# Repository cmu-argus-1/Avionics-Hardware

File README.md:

# AVIONICS_HARDWARE_DEV

Hardware boards devolepment repository.
1. Magnetic torque coil board
2. Power board
3. ML board
4. Camera board

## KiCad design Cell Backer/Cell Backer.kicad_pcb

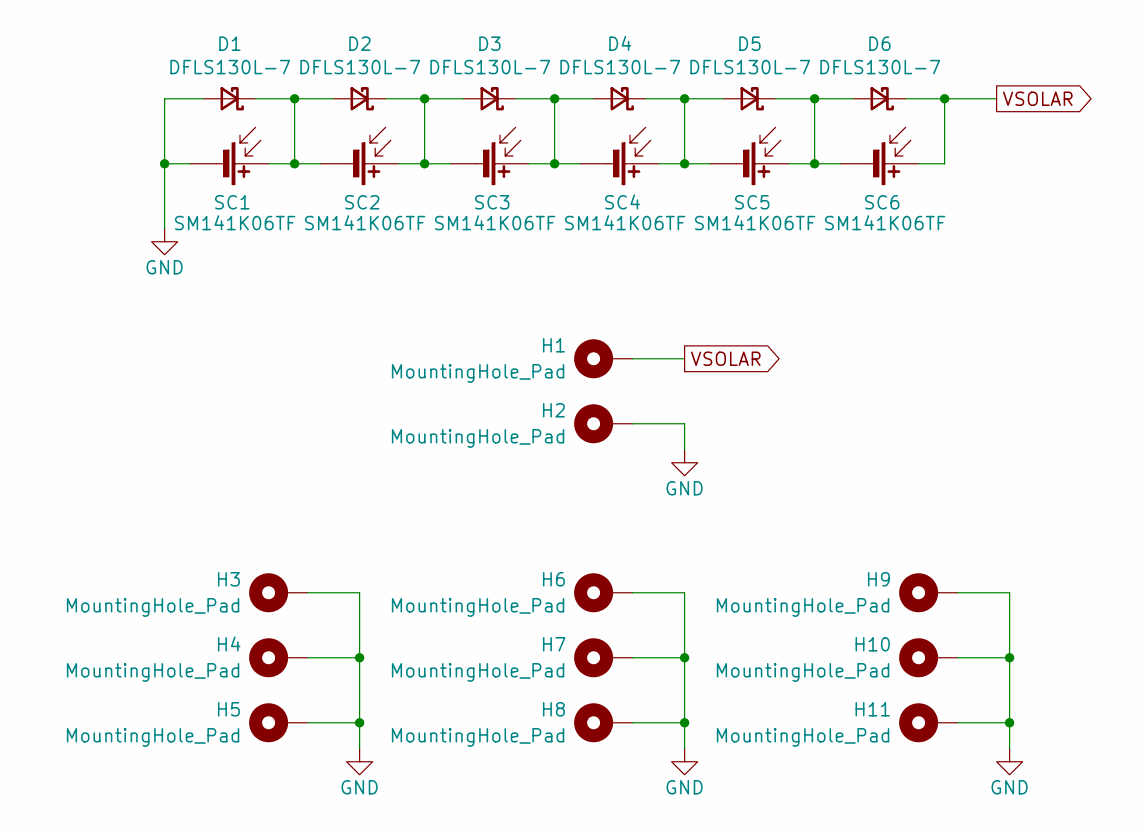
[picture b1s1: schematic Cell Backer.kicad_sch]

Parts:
D1, D2, D3, D4, D5, D6: DFLS130L-7; D_PowerDI-123
H1, H2: MountingHole_Pad; MountingHole_1.5mm
H3, H4, H5, H6, H7, H8, H9, H10, H11: MountingHole_Pad; MountingHole_1mm
SC1, SC2, SC3, SC4, SC5, SC6: SM141K06TF

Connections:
GND: D1.2 (A), H2.1, H3.1, H4.1, H5.1, H6.1, H7.1, H8.1, H9.1, H10.1, H11.1, SC1.2 (-)
unnamed: D1.1 (K), D2.2 (A), SC1.1 (+), SC2.2 (-)
unnamed: D2.1 (K), D3.2 (A), SC2.1 (+), SC3.2 (-)
unnamed: D3.1 (K), D4.2 (A), SC3.1 (+), SC4.2 (-)
unnamed: D4.1 (K), D5.2 (A), SC4.1 (+), SC5.2 (-)
unnamed: D5.1 (K), D6.2 (A), SC5.1 (+), SC6.2 (-)
VSOLAR: D6.1 (K), H1.1, SC6.1 (+)

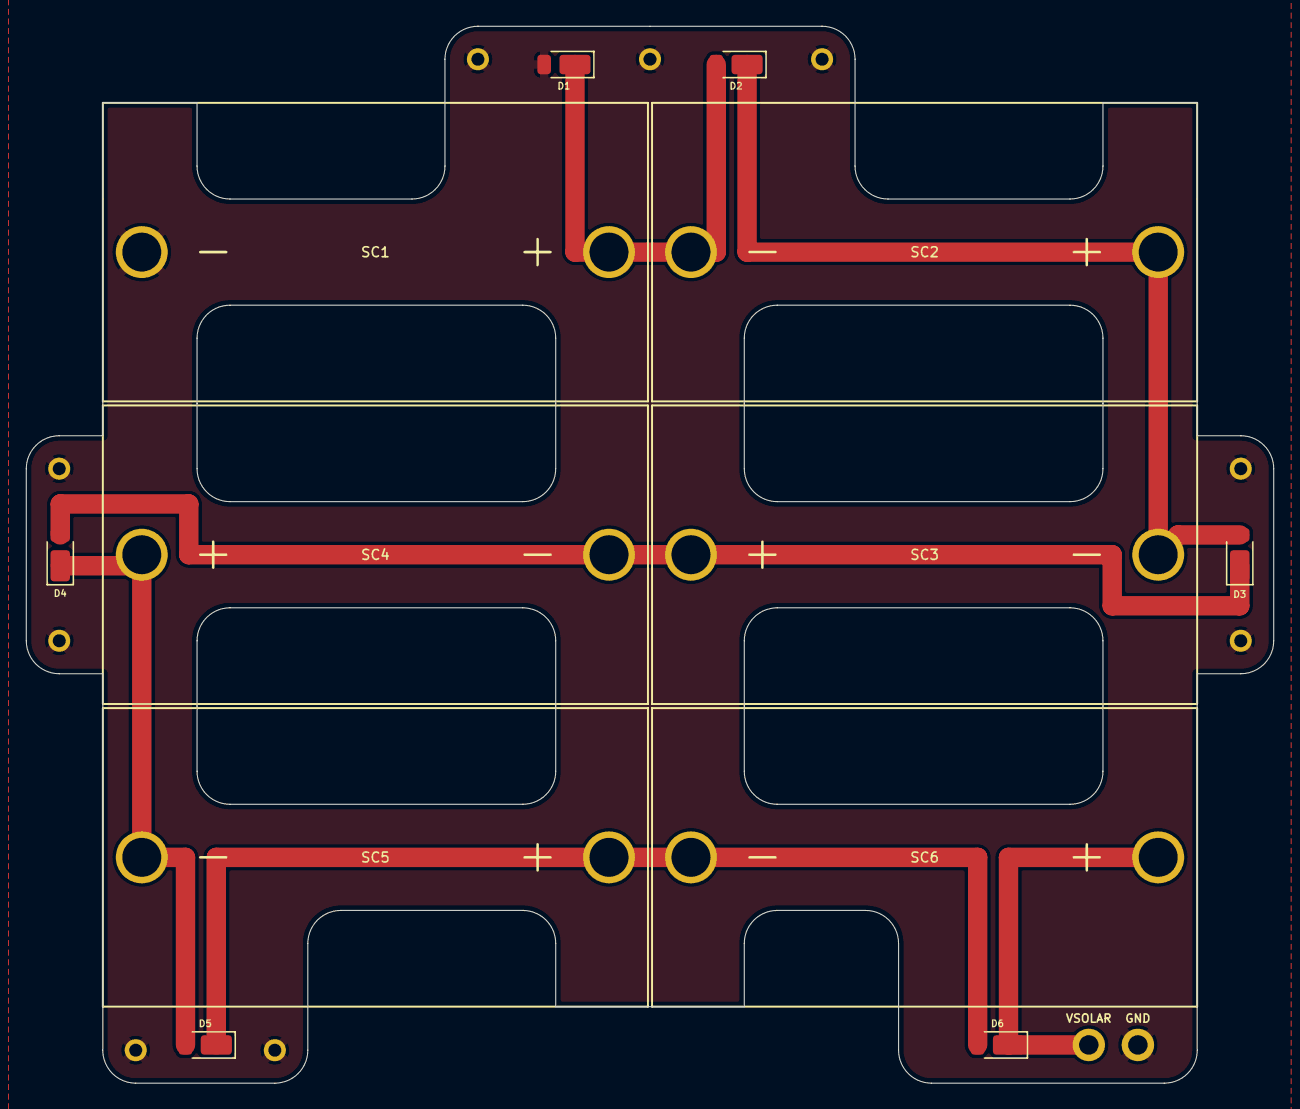
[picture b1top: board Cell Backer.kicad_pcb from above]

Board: 2 copper layers, 96.1 x 81.4 mm, 23 parts (0 on the bottom side), 7 nets.

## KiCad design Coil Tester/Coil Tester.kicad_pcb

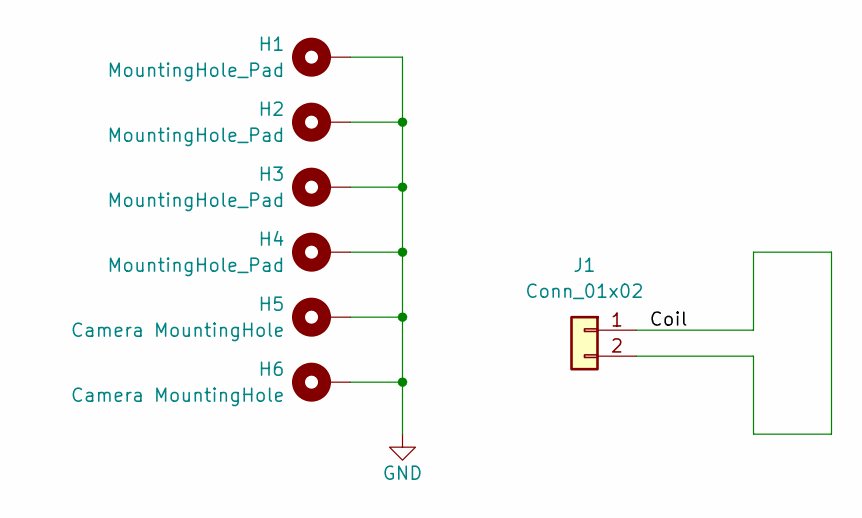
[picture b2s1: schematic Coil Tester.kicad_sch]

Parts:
H1, H2, H3, H4: MountingHole_Pad; MountingHole_3.2mm_M3_DIN965_Pad_TopBottom
H5, H6: Camera MountingHole; MountingHole_3mm
J1: Conn_01x02; PinHeader_1x02_P2.54mm_Vertical

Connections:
/Coil: J1.1, J1.2
GND: H1.1, H2.1, H3.1, H4.1, H5.1, H6.1

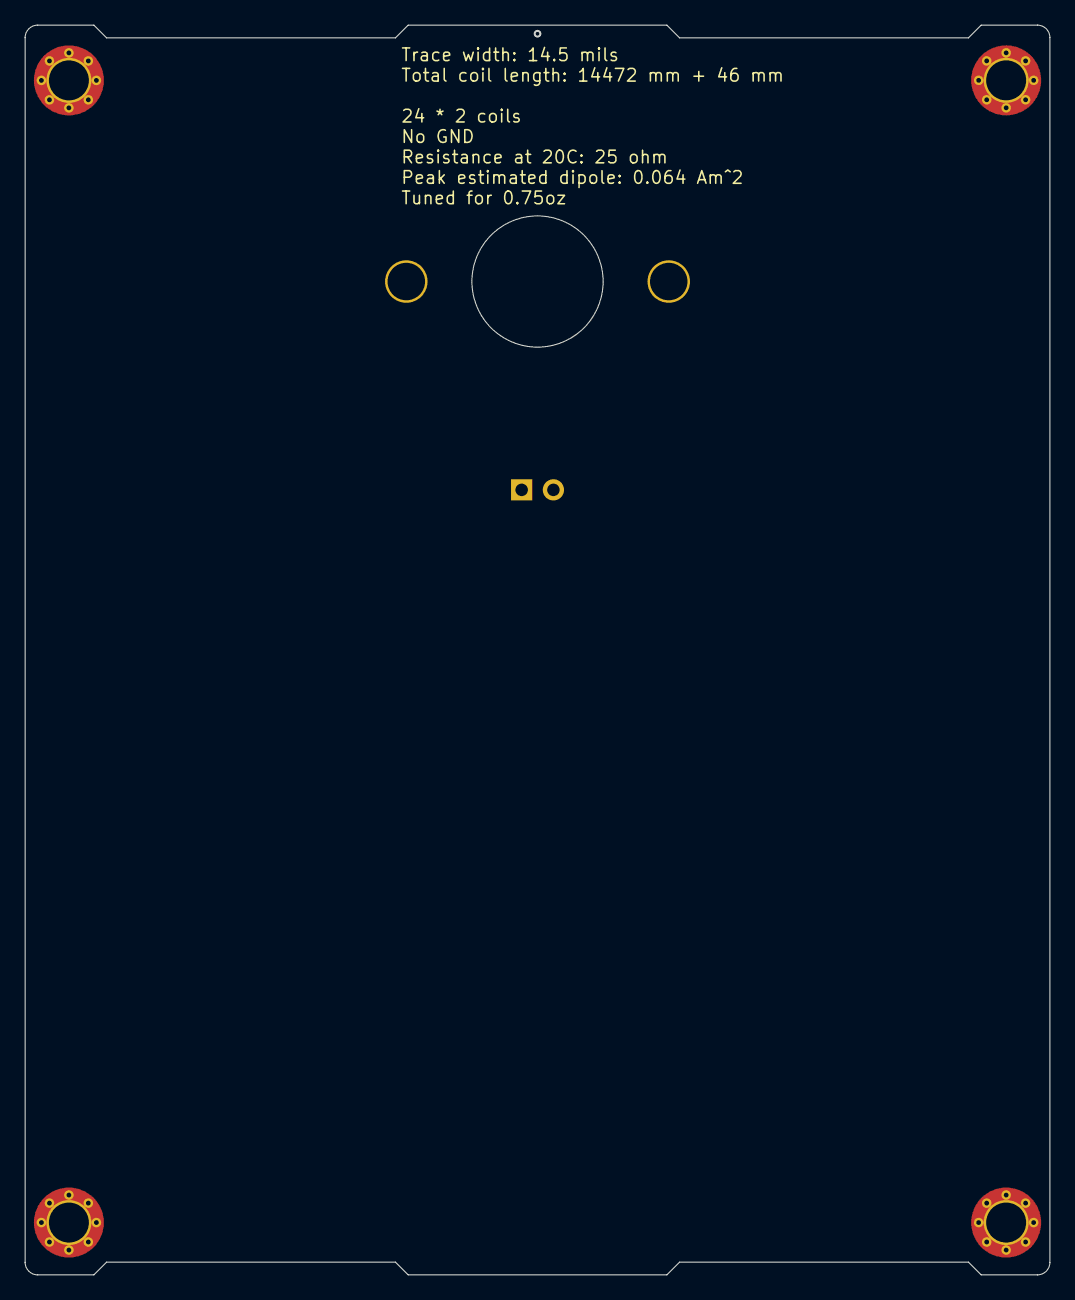
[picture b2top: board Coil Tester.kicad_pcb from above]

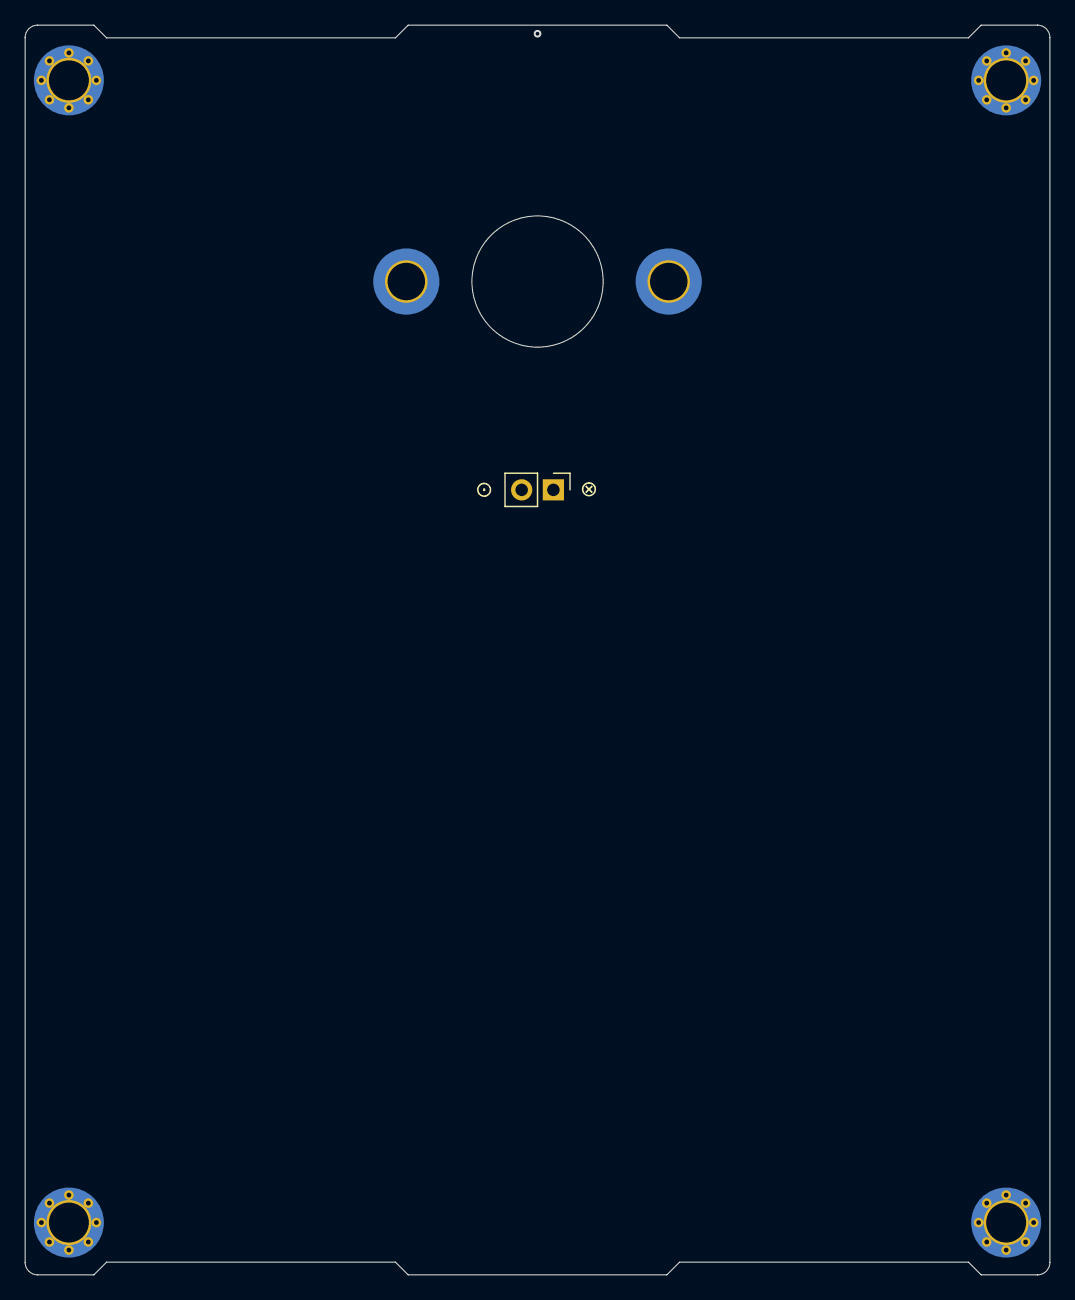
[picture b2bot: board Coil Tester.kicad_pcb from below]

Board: 4 copper layers, 82.0 x 100.0 mm, 7 parts (3 on the bottom side), 2 nets.

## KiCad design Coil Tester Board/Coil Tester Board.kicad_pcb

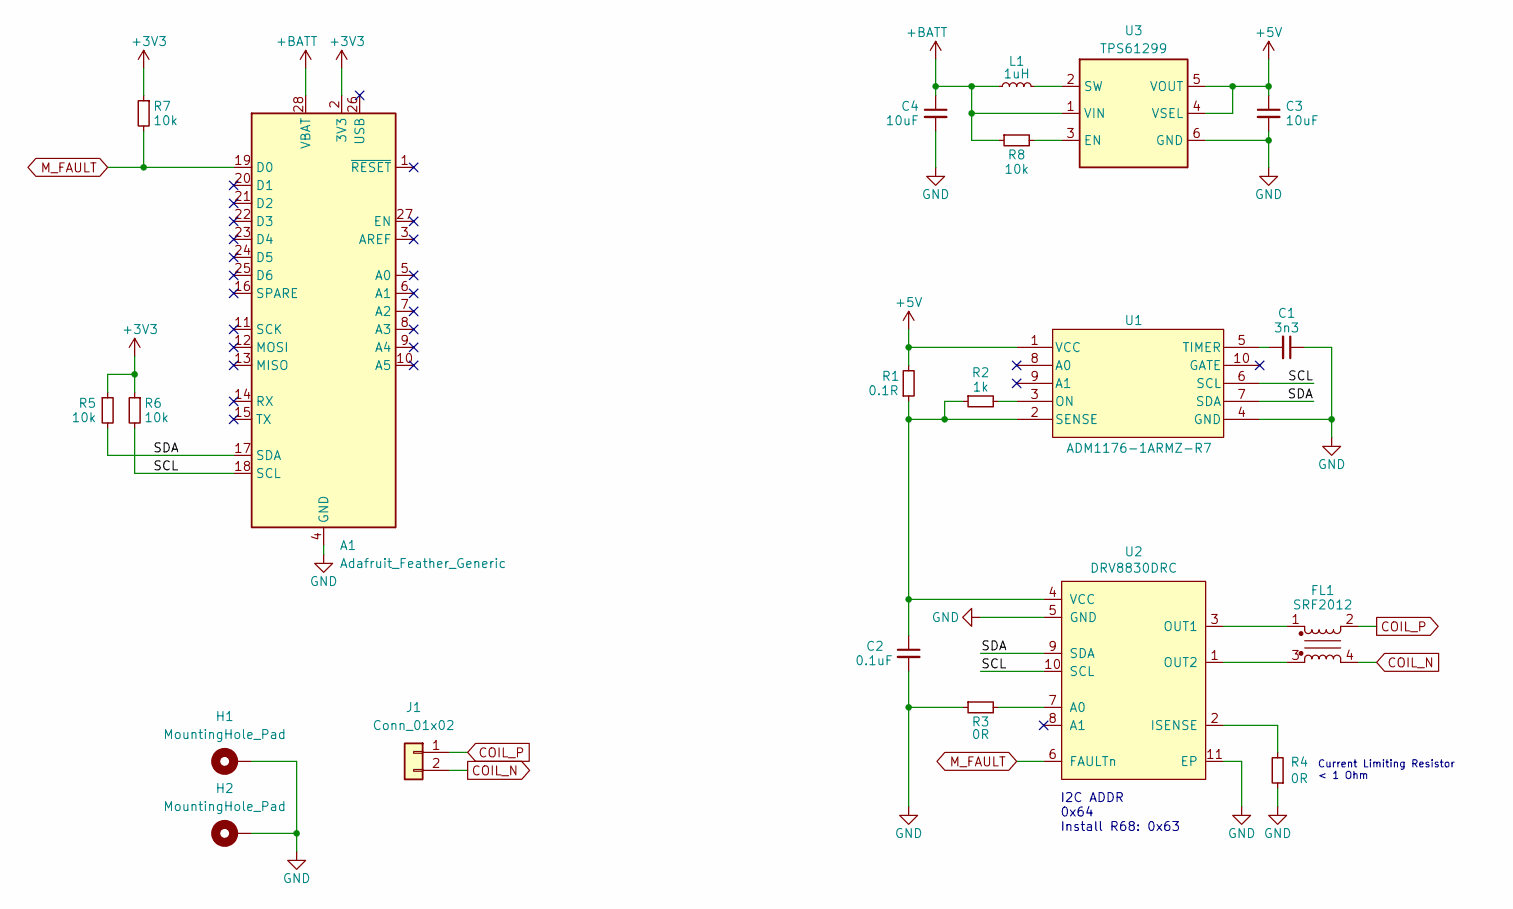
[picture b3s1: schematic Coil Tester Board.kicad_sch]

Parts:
A1: Adafruit_Feather_Generic; Adafruit_Feather
C1: 3n3; C_0603_1608Metric
C2: 0.1uF; C_0805_2012Metric
C3, C4: 10uF; C_0805_2012Metric
FL1: SRF2012
H1, H2: MountingHole_Pad; MountingHole_2.2mm_M2_DIN965_Pad
J1: Conn_01x02; PinHeader_1x02_P2.54mm_Vertical
L1: 1uH; L_1008_2520Metric_Pad1.43x2.20mm_HandSolder
R1: 0.1R; R_2512_6332Metric
R2: 1k; R_0603_1608Metric
R3, R4: 0R; R_0603_1608Metric
R5, R6, R7, R8: 10k; R_0603_1608Metric
U1: ADM1176-1ARMZ-R7; MSOP-10_3x3mm_P0.5mm; Manufacturer_Part_Number ADM1176-1ARMZ-R7
U2: DRV8830DRC; VSON-10-1EP_3x3mm_P0.5mm_EP1.65x2.4mm
U3: TPS61299; SOT-563

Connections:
+3V3: A1.2 (3V3), R5.1, R6.1, R7.1; also elsewhere on the board
+5V: C3.1, R1.2, U1.1 (VCC), U3.4 (VSEL), U3.5 (VOUT)
+BATT: A1.28 (VBAT), C4.1, L1.1, R8.1, U3.1 (VIN)
/SCL: A1.18 (SCL), R6.2, U1.6 (SCL), U2.10 (SCL)
/SDA: A1.17 (SDA), R5.2, U1.7 (SDA), U2.9 (SDA); also elsewhere on the board
COIL_N: FL1.4, J1.2
COIL_P: FL1.2, J1.1
GND: A1.4 (GND), C1.1, C2.2, C3.2, C4.2, H1.1, H2.1, R3.1, R4.1, U1.4 (GND), U2.5 (GND), U2.11 (EP), U3.6 (GND)
M_FAULT: A1.19 (D0), R7.2, U2.6 (FAULTn)
unnamed: R2.2, U1.3 (ON)
unnamed: C2.1, R1.1, R2.1, U1.2 (SENSE), U2.4 (VCC)
unnamed: C1.2, U1.5 (TIMER)
unnamed: R3.2, U2.7 (A0)
unnamed: R4.2, U2.2 (ISENSE)
unnamed: FL1.1, U2.3 (OUT1)
unnamed: FL1.3, U2.1 (OUT2)
unnamed: R8.2, U3.3 (EN)
unnamed: L1.2, U3.2 (SW)

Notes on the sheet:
Current Limiting Resistor < 1 Ohm
I2C ADDR 0x64 Install R68: 0x63

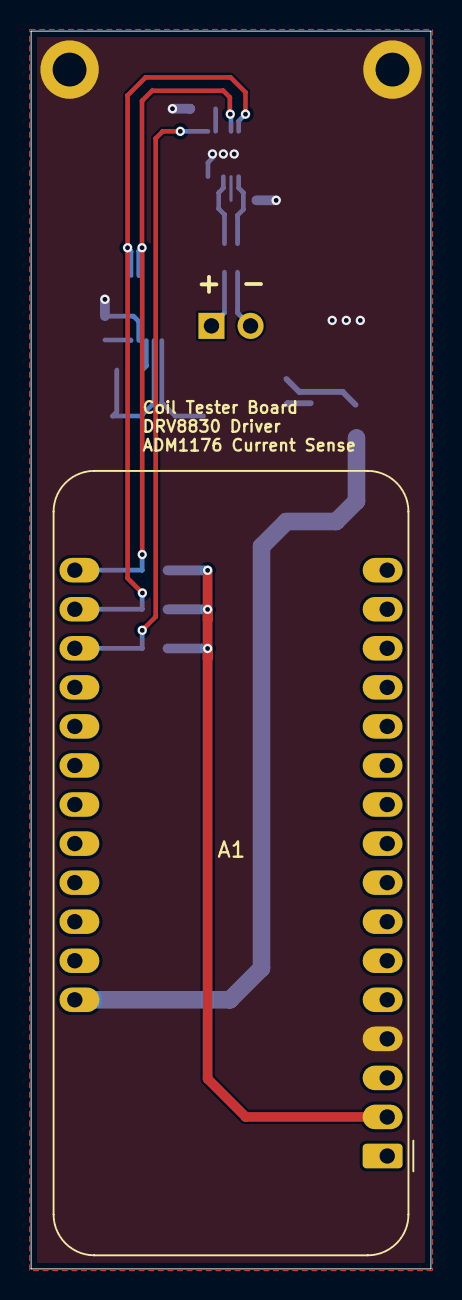
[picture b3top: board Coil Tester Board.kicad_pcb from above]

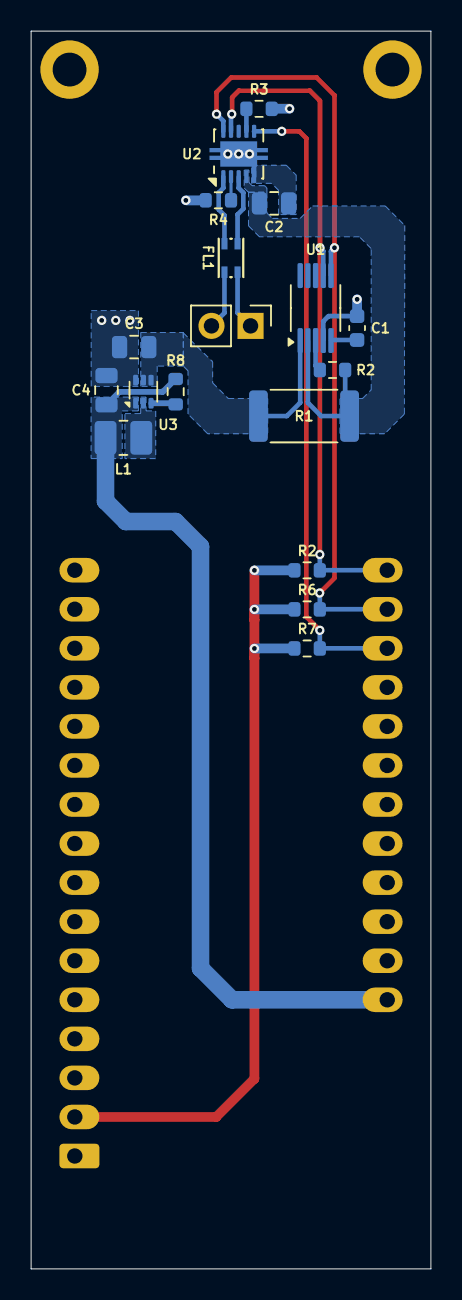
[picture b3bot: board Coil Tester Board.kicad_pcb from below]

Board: 2 copper layers, 26.0 x 80.5 mm, 21 parts (18 on the bottom side), 18 nets.

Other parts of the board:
R2#2: 10k; R_0603_1608Metric

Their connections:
+3V3: R2#2.1; also elsewhere on the board
/SDA: R2#2.2; also elsewhere on the board

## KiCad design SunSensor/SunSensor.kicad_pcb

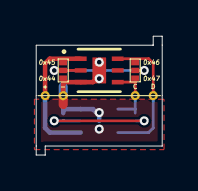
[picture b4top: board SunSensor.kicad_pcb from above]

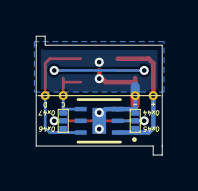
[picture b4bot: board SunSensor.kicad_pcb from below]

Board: 2 copper layers, 7.0 x 6.6 mm, 10 parts (5 on the bottom side), 5 nets.

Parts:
H1, H2: CastellatedHole
H3, H4: MountingHole_Pad; CastellatedHole
JP1, JP2: Jumper_3_Open; SolderJumper-3_P1.3mm_Open_RoundedPad1.0x1.5mm
JP1#2, JP2#2: SolderJumper-3_P1.3mm_Open_RoundedPad1.0x1.5mm
U1, U1#2: OPT4003DNPRQ1; OPT4003

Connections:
+3.3V: H1.1, JP1.3 (B), JP1#2.3 (B), U1.1 (VDD), U1#2.1 (VDD)
/ADDR: JP1.2 (C), JP1#2.2 (C), JP2.2 (C), JP2#2.2 (C), U1.2 (ADDR), U1#2.2 (ADDR)
/SCL: H4.1, JP2.1 (A), JP2#2.1 (A), U1.4 (SCL), U1#2.4 (SCL)
/SDA: H3.1, JP2.3 (B), JP2#2.3 (B), U1.6 (SDA), U1#2.6 (SDA)
GND: H2.1, JP1.1 (A), JP1#2.1 (A), U1.3 (GND), U1.7 (EPAD), U1#2.3 (GND), U1#2.7 (EPAD)

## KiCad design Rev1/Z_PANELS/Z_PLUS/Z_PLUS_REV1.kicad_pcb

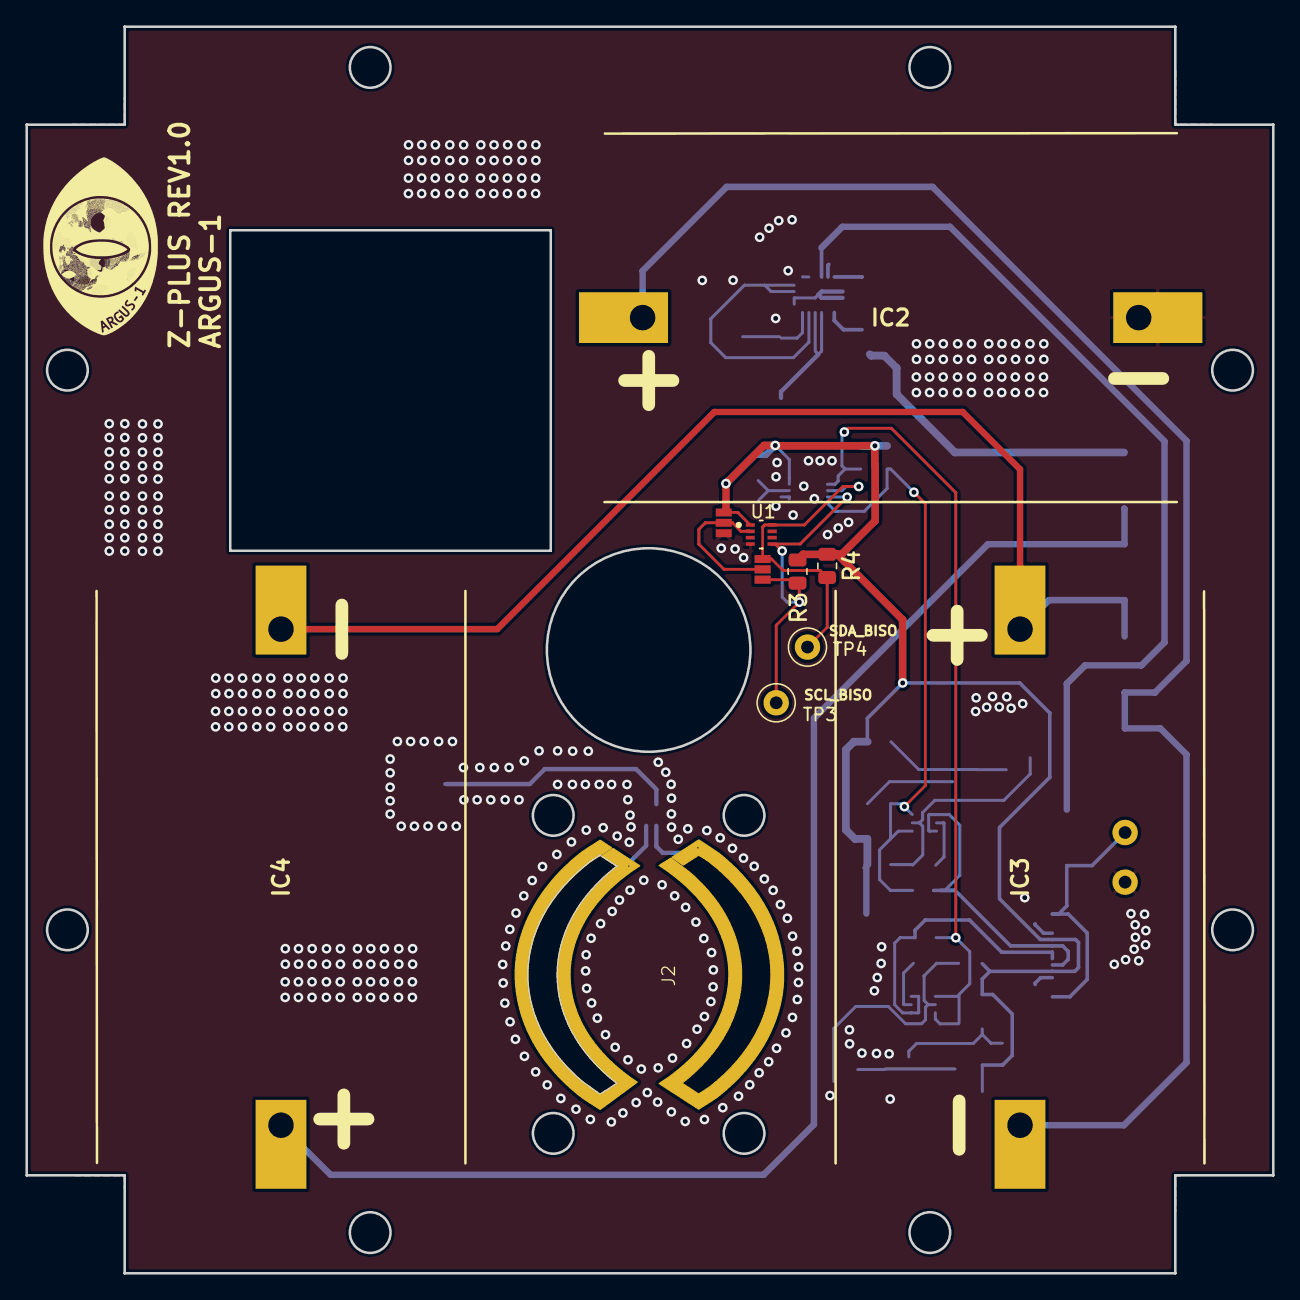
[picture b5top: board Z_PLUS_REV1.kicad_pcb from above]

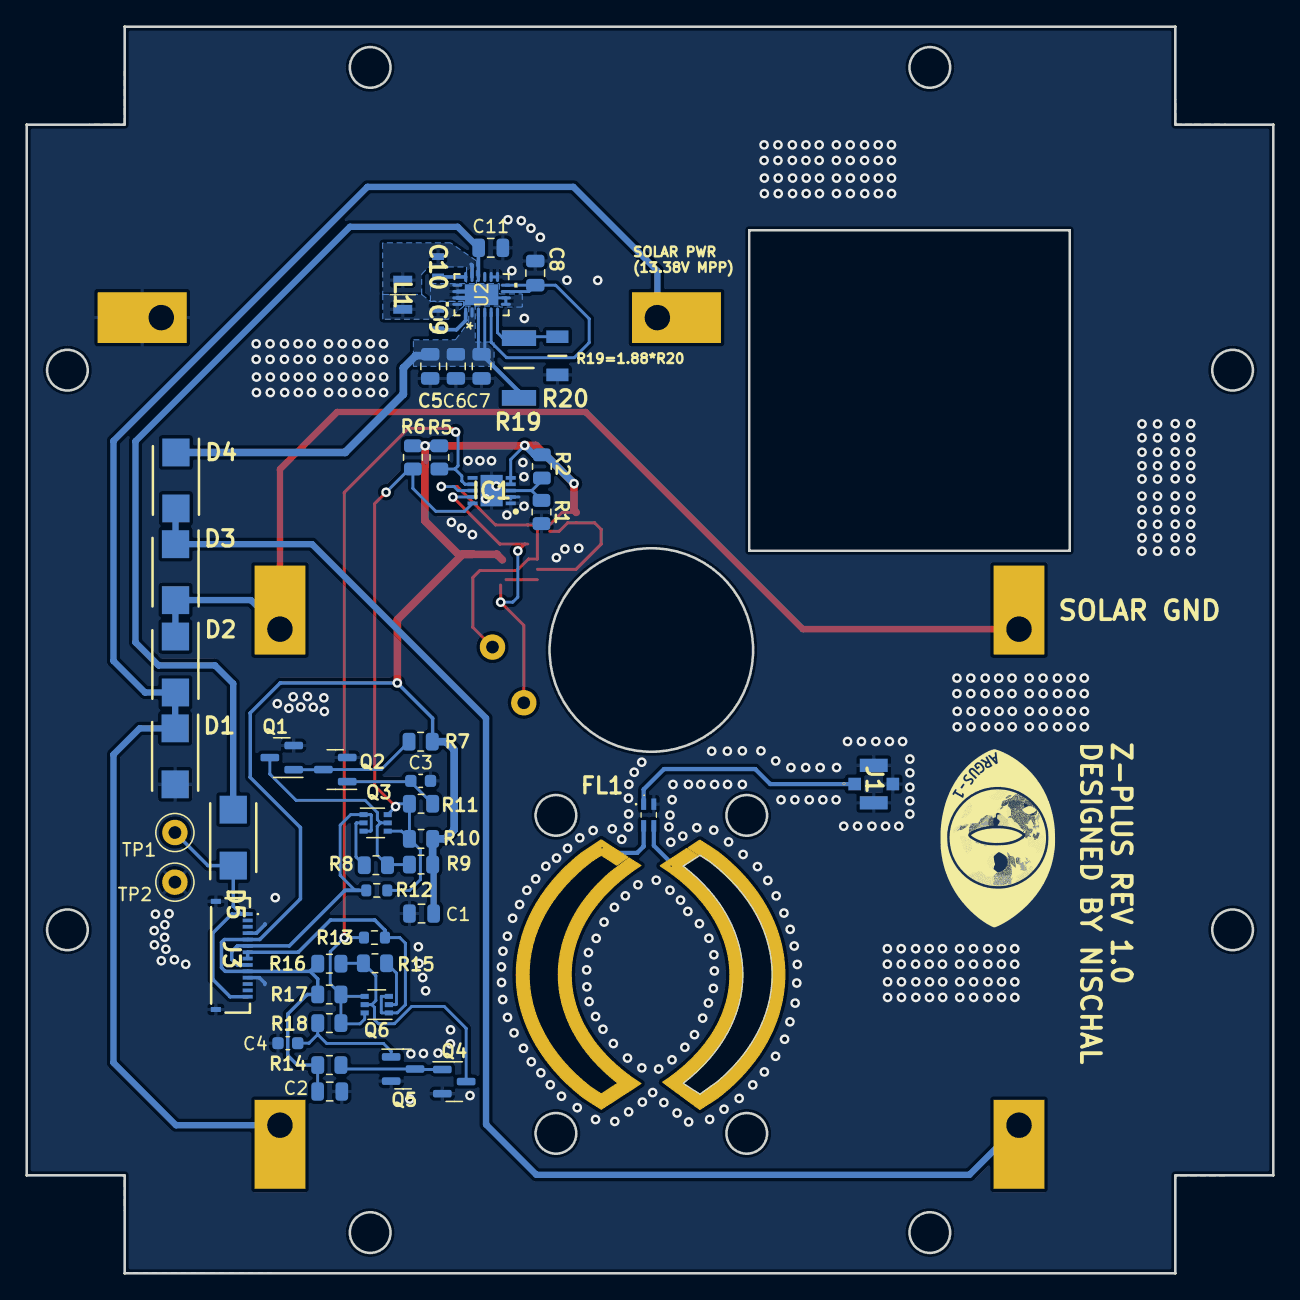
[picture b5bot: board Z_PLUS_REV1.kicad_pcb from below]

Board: 2 copper layers, 98.0 x 98.0 mm, 61 parts (49 on the bottom side), 33 nets.

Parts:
., .#2: .; ARGUS_LOGO
C1, C2: 0.1uF; C_0805_2012Metric
C3, C4: 10nF; C_0603_1608Metric
C5, C8: 4.7uF; C_0805_2012Metric
C6, C11: 47uF; C_0805_2012Metric
C7: 1uF; C_0805_2012Metric
C9, C10: CGA3E2X7R1H223K080AA; CAPC1608X90N
D1, D2, D3, D4, D5: LSM115JE3_TR13; DIOM5436X330N
FL1: DXW21HN5011BL
IC1: LTC4316IDD#PBF; SON50P300X300X85-11N-D
IC2, IC3, IC4: SM141K08TFV; SODFL520290X120N
J1: 73412-0114; 73412-0110
J2: Tape_Measure_Antenna; Radio_antenna
J3: F3311A7H121014E200
JP1, JP2: SMT-JUMPER_3_NO_NO-SILK
L1: LQM2HPN4R7MG0L; LQM2HPN1R0MG0L
Q1, Q2, Q4, Q5: BSS138; SOT-23
Q3, Q6: MBT2222ADW1T1; SOT-363_SC-70-6
R1: 182K; R_0805_2012Metric
R2: 976k; R_0805_2012Metric
R3, R4, R5, R6, R7, R9, R10, R14, R16, R17: 10K; R_0805_2012Metric
R8, R15: 600; R_0805_2012Metric
R11, R18: 100K; R_0805_2012Metric
R12, R13: 0; R_0603_1608Metric
R19: 12M; RESC5025X70N
R20: 1M; RESC3116X65N
TP1: VSOLAR; TestPoint_Loop_D1.80mm_Drill1.0mm_Beaded
TP2: GND; TestPoint_Loop_D1.80mm_Drill1.0mm_Beaded
TP3, TP4: TestPoint; TestPoint_Loop_D1.80mm_Drill1.0mm_Beaded
U1: OPT4001DTST; DTS0008A-MFG
U2: LTC3130EUDC-1-PBF; UDC_20_ADI

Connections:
+3.3V: C1.1, C2.1, IC1.4 (VCC), IC1.5 (ENABLE), J3.5, J3.10, JP2.3 (B), R2.1, R3.2, R4.2, R5.2, R6.2, R7.2, R9.1, R10.2, R14.2, R16.1, R17.2, U1.1 (VDD)
/1+: FL1.3, J2.2
/1-: FL1.2, J2.1
/SOLAR_PANEL_ELECTRONICS/7023_vout: D3.1, D4.2, IC4.1 (POS)
/SOLAR_PANEL_ELECTRONICS/MPPC1: R19.1, R20.2, U2.6 (MPPC)
GND: C1.2, C2.2, C3.2, C4.2, C5.2, C6.2, C7.2, C8.2, C11.2, D1.2, FL1.4, IC1.1 (GND_1), IC1.2 (XORH), IC1.11 (GND_2), IC2.2 (NEG), J1.2 (GND_1), J1.3 (GND_2), J1.4 (GND_3), J3.4, J3.11, J3.MP1, J3.MP2, JP2.1 (A), Q1.2 (S), Q2.2 (S), Q4.2 (S), Q5.2 (S), R1.2, R20.1, TP2.1, U1.4 (GND), U2.7 (GND), U2.8 (GND), U2.11 (MODE), U2.12 (EXTVCC), U2.17 (NC), U2.18 (PGND), U2.19 (PGND), U2.21 (PAD)
unnamed: IC1.3 (XORL), R1.1, R2.2
unnamed: D1.1, D2.2, IC2.1 (POS), IC3.2 (NEG)
unnamed: D2.1, D3.2, IC3.1 (POS), IC4.2 (NEG)
unnamed: FL1.1, J1.1 (SIGNAL)
unnamed: JP1.2 (C), JP2.2 (C), U1.2 (ADDR)
unnamed: Q1.3 (D), Q3.5 (B2), R8.1, R9.2
unnamed: Q1.1 (G), Q2.3 (D), R7.1
unnamed: C3.1, Q2.1 (G), R11.1
unnamed: Q3.2 (B1), R8.2
unnamed: Q4.3 (D), Q6.5 (B2), R15.2, R16.2
unnamed: Q4.1 (G), Q5.3 (D), R14.1
unnamed: C4.1, Q5.1 (G), R18.1
unnamed: Q6.2 (B1), R15.1
unnamed: C9.2, U2.1 (BST1)
unnamed: C10.2, U2.16 (BST2)
unnamed: C5.1, C6.1, C7.1, D4.1, R19.2, U2.2 (PVIN), U2.3 (VIN), U2.4 (RUN)
unnamed: C9.1, L1.2, U2.20 (SW1)
unnamed: C10.1, L1.1, U2.15 (SW2)
unnamed: C8.1, U2.5 (VCC), U2.9 (VS2/FB), U2.10 (VS1/ILIM)
unnamed: C11.1, D5.2, U2.14 (VOUT)
SCL1_b4iso: J3.6, J3.9, Q3.1 (E1), Q3.3 (C2), R12.1
SCL_4001: IC1.9 (SCLOUT), JP1.3 (B), R3.1, TP3.1, U1.5 (SCL)
SCL_SUN: IC1.10 (SCLIN), Q3.4 (E2), Q3.6 (C1), R6.1, R10.1, R11.2, R12.2
SDA1_b4iso: J3.7, J3.8, Q6.1 (E1), Q6.3 (C2), R13.1
SDA_4001: IC1.8 (SDAOUT), JP1.1 (A), R4.1, TP4.1, U1.8 (SDA)
SDA_SUN: IC1.7 (SDAIN), Q6.4 (E2), Q6.6 (C1), R5.1, R13.2, R17.1, R18.2
VSOLAR: D5.1, J3.1, J3.14, TP1.1

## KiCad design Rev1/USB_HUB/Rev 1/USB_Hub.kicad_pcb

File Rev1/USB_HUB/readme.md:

# Check off list
## Please check the box add your name and time.
## add "[x]" for checking off a list item, please make sure you edit the readme file and then commit and push or else the change wont take place.

- [x] Design Signoff made by Rohit Bangal at time 02:12 PM and date 02/27/2024
- [x] Avionics Signoff made by Harry Rosmann at time 4:11 PM and date 2/27/2024
- [x] Mechanical Signoff made by Allison Weller at time 5:20 PM and date 2/28/2024
- [ ] TA signoff by __ at time __ and date __
- [ ] Board list sent by -- to -- at time __ and date __
- [ ] Parts list sent by -- to -- at time __ and date __
- [ ] Board ordered by -- at time __ and date __
- [ ] Parts Ordered by -- at time __ and date __
- [ ] Board received -- at time __ and date __
- [ ] Parts Received  at time __ and date __
- [ ] Boards Built at time __ and date __
- [ ] Boards tested at time __ and date __
- [ ] Boards ready at time __ and date __

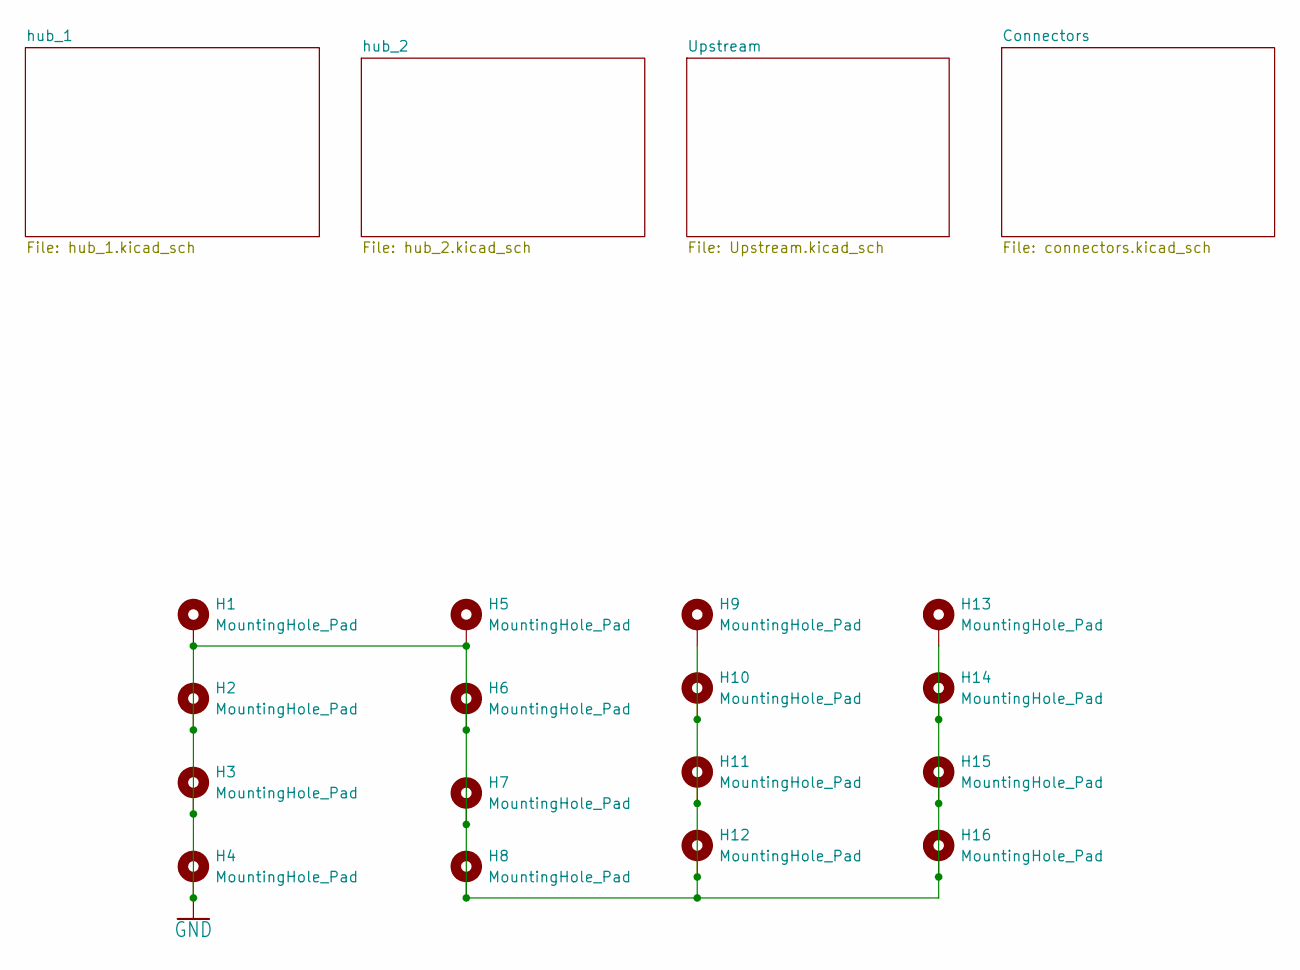
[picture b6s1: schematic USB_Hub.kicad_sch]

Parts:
H1, H2, H3, H4: MountingHole_Pad; MountingHole_3.2mm_M3_DIN965_Pad
H5, H6, H7, H8: MountingHole_Pad; MountingHole_2.2mm_M2_DIN965_Pad
H9, H10, H11, H12, H13, H14, H15, H16: MountingHole_Pad; MountingHole_USB

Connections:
GND: H1.1, H2.1, H3.1, H4.1, H5.1, H6.1, H7.1, H8.1, H9.1, H10.1, H11.1, H12.1, H13.1, H14.1, H15.1, H16.1; also elsewhere on the board

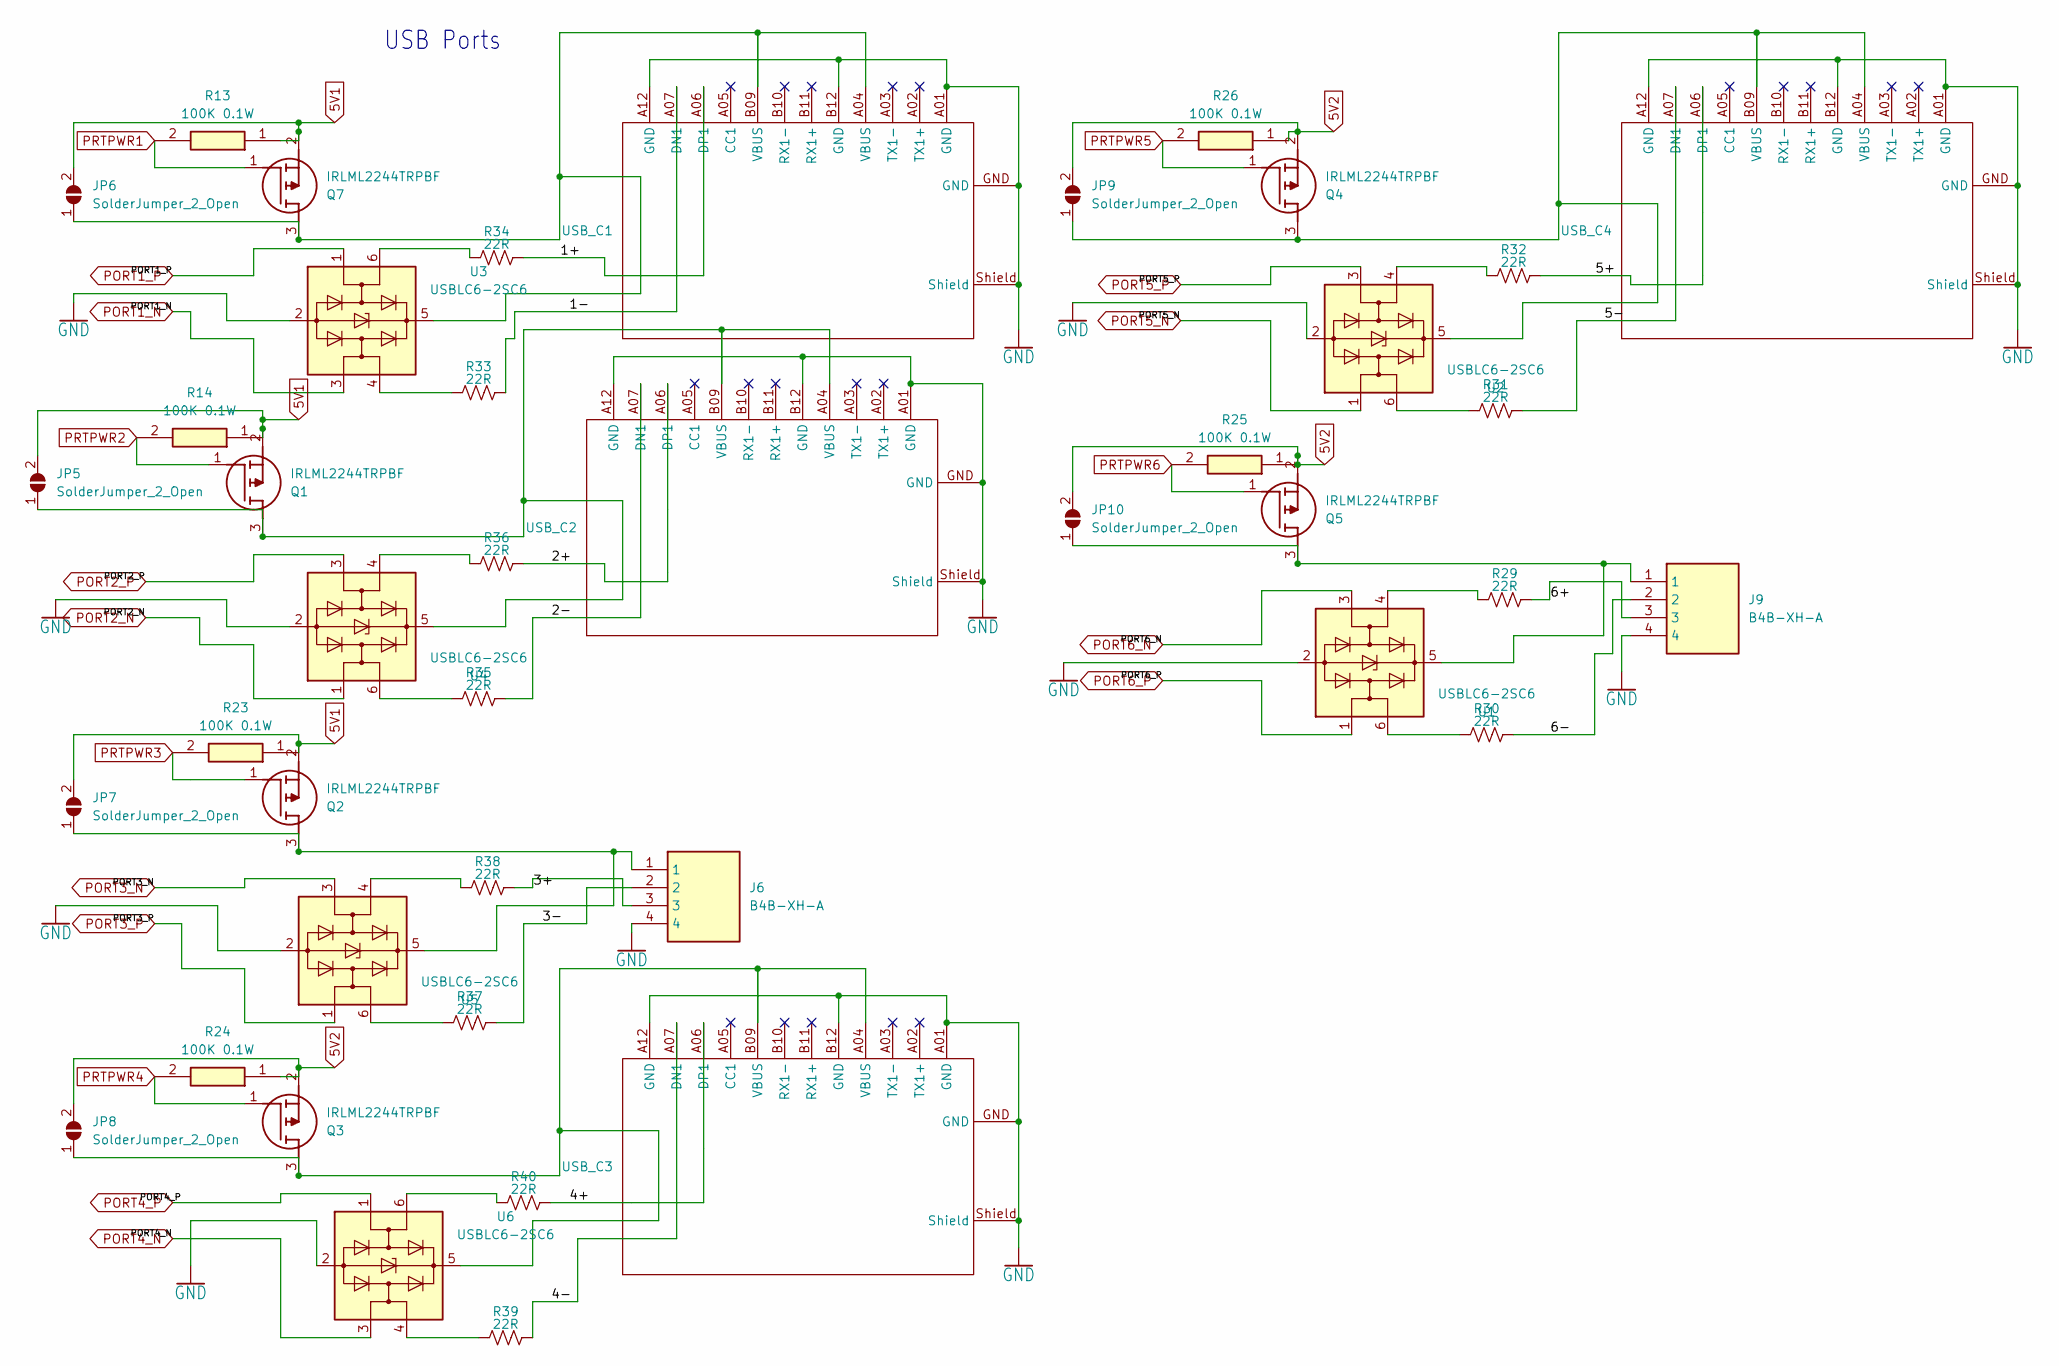
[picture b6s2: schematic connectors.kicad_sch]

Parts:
J6, J9: B4B-XH-A; B4BXHA; Manufacturer_Part_Number B4B-XH-A
JP5, JP6, JP7, JP8, JP9, JP10: SolderJumper_2_Open; SolderJumper-2_P1.3mm_Open_Pad1.0x1.5mm
Q1, Q2, Q3, Q4, Q5, Q7: IRLML2244TRPBF; SOT95P237X112-3N; Manufacturer_Part_Number IRLML2244TRPBF; Mouser Part Number 942-IRLML2244TRPBF
R13, R14, R23, R24, R25, R26: 100K 0.1W; RESC1608X55N; Manufacturer_Part_Number RMCF0603FT100K; Mouser Part Number 708-RMCF0603FT100K
R29, R30, R31, R32, R33, R34, R35, R36, R37, R38, R39, R40: 22R; R_0603_1608Metric
U1, U2, U3, U4, U5, U6: USBLC6-2SC6; SOT-23-6
USB_C1, USB_C2, USB_C3, USB_C4: PLUG-USBC-121SMT-4BS2S

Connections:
5V1: JP5.2 (B), JP6.2 (B), JP7.2 (B), Q1.2 (S), Q2.2 (S), Q7.2 (S), R13.1, R14.1, R23.1; also elsewhere on the board
5V2: JP8.2 (B), JP9.2 (B), JP10.2 (B), Q3.2 (S), Q4.2 (S), Q5.2 (S), R24.1, R25.1, R26.1; also elsewhere on the board
/Connectors/1+: R34.1, USB_C1.A06 (DP1)
/Connectors/1-: R33.1, USB_C1.A07 (DN1)
/Connectors/2+: R36.1, USB_C2.A06 (DP1)
/Connectors/2-: R35.1, USB_C2.A07 (DN1)
/Connectors/3+: J6.3, R38.1
/Connectors/3-: J6.2, R37.1
/Connectors/4+: R40.1, USB_C3.A06 (DP1)
/Connectors/4-: R39.1, USB_C3.A07 (DN1)
/Connectors/5+: R32.1, USB_C4.A06 (DP1)
/Connectors/5-: R31.1, USB_C4.A07 (DN1)
/Connectors/6+: J9.3, R29.1
/Connectors/6-: J9.2, R30.1
GND: J6.4, J9.4, U1.2 (GND), U2.2 (GND), U3.2 (GND), U4.2 (GND), U5.2 (GND), U6.2 (GND), USB_C1.A01 (GND), USB_C1.A12 (GND), USB_C1.B12 (GND), USB_C1.GND, USB_C1.Shield, USB_C2.A01 (GND), USB_C2.A12 (GND), USB_C2.B12 (GND), USB_C2.GND, USB_C2.Shield, USB_C3.A01 (GND), USB_C3.A12 (GND), USB_C3.B12 (GND), USB_C3.GND, USB_C3.Shield, USB_C4.A01 (GND), USB_C4.A12 (GND), USB_C4.B12 (GND), USB_C4.GND, USB_C4.Shield; also elsewhere on the board
unnamed: JP5.1 (A), Q1.3 (D), U4.5 (VBUS), USB_C2.A04 (VBUS), USB_C2.B09 (VBUS)
unnamed: JP6.1 (A), Q7.3 (D), U3.5 (VBUS), USB_C1.A04 (VBUS), USB_C1.B09 (VBUS)
unnamed: J6.1, JP7.1 (A), Q2.3 (D), U5.5 (VBUS)
unnamed: JP8.1 (A), Q3.3 (D), U6.5 (VBUS), USB_C3.A04 (VBUS), USB_C3.B09 (VBUS)
unnamed: JP9.1 (A), Q4.3 (D), U2.5 (VBUS), USB_C4.A04 (VBUS), USB_C4.B09 (VBUS)
unnamed: J9.1, JP10.1 (A), Q5.3 (D), U1.5 (VBUS)
unnamed: R29.2, U1.4 (I/O2)
unnamed: R30.2, U1.6 (I/O1)
unnamed: R31.2, U2.6 (I/O1)
unnamed: R32.2, U2.4 (I/O2)
unnamed: R33.2, U3.4 (I/O2)
unnamed: R34.2, U3.6 (I/O1)
unnamed: R35.2, U4.6 (I/O1)
unnamed: R36.2, U4.4 (I/O2)
unnamed: R37.2, U5.6 (I/O1)
unnamed: R38.2, U5.4 (I/O2)
unnamed: R39.2, U6.4 (I/O2)
unnamed: R40.2, U6.6 (I/O1)
PORT1_N: U3.3 (I/O2); also elsewhere on the board
PORT1_P: U3.1 (I/O1); also elsewhere on the board
PORT2_N: U4.1 (I/O1); also elsewhere on the board
PORT2_P: U4.3 (I/O2); also elsewhere on the board
PORT3_N: U5.3 (I/O2); also elsewhere on the board
PORT3_P: U5.1 (I/O1); also elsewhere on the board
PORT4_N: U6.3 (I/O2); also elsewhere on the board
PORT4_P: U6.1 (I/O1); also elsewhere on the board
PORT5_N: U2.1 (I/O1); also elsewhere on the board
PORT5_P: U2.3 (I/O2); also elsewhere on the board
PORT6_N: U1.3 (I/O2); also elsewhere on the board
PORT6_P: U1.1 (I/O1); also elsewhere on the board
PRTPWR1: Q7.1 (G), R13.2; also elsewhere on the board
PRTPWR2: Q1.1 (G), R14.2; also elsewhere on the board
PRTPWR3: Q2.1 (G), R23.2; also elsewhere on the board
PRTPWR4: Q3.1 (G), R24.2; also elsewhere on the board
PRTPWR5: Q4.1 (G), R26.2; also elsewhere on the board
PRTPWR6: Q5.1 (G), R25.2; also elsewhere on the board

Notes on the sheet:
USB Ports
